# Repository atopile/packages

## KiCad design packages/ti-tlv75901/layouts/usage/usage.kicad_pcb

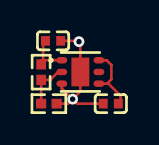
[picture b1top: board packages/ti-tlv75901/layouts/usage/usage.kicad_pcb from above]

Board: 2 copper layers, 5 parts (0 on the bottom side), 5 nets.

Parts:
C1, C2: 1µF ±10%; C0402
R1: 9.09kΩ ±1%; R0402
R2: 1.82kΩ ±1%; R0402
U1: WSON-6_L2.0-W2.0-P0.65-TL-EP

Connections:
hv: C1.1, U1.4, U1.6
lv: C1.2, U1.3
power-hv: C2.1, R1.1, U1.1
power-lv: C2.2, R2.2, U1.7
ref_out-hv: R1.2, R2.1, U1.2

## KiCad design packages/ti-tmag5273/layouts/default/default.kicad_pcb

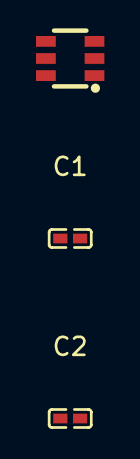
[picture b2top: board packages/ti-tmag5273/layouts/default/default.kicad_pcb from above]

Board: 2 copper layers, 3 parts (0 on the bottom side), 2 nets, no tracks yet.

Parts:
C1: 10nF ±10% 6.3V X7R; C0402
C2: 100nF ±10% 6.3V X7R; C0402
U1: SOT-23-6_L2.9-W1.6-P0.95-LS2.8-BR

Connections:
VCC: C1.1, C2.1, U1.4
gnd: C1.2, C2.2, U1.2

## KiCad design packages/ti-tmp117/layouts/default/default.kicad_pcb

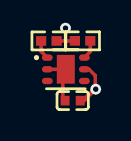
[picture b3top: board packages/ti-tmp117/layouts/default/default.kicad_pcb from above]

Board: 2 copper layers, 4 parts (0 on the bottom side), 4 nets.

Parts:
C1: 100nF; C0402
R1, R2: 10kΩ; R0402
U1: WSON-6_L2.0-W2.0-P0.65-TL-EP

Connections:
SCL: R1.1, U1.1
SDA: R2.1, U1.6
hv: C1.1, R1.2, R2.2, U1.5
lv: C1.2, U1.2, U1.4, U1.7

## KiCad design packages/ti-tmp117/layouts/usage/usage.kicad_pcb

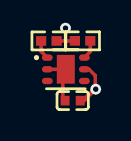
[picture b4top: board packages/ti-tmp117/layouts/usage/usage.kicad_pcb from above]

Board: 2 copper layers, 4 parts (0 on the bottom side), 4 nets.

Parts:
C1: 100nF; C0402
R3, R4: 10kΩ; R0402
U1: WSON-6_L2.0-W2.0-P0.65-TL-EP

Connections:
SCL: R3.1, U1.1
SDA: R4.1, U1.6
hv: C1.1, R3.2, R4.2, U1.5
lv: C1.2, U1.2, U1.4, U1.7

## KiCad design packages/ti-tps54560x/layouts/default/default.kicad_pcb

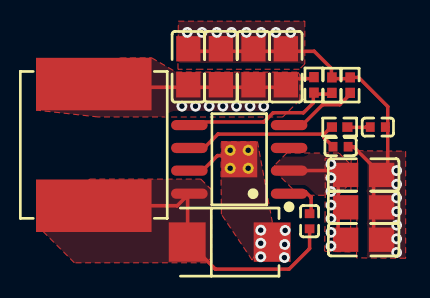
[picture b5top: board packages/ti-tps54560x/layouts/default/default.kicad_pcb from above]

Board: 2 copper layers, 17 parts (0 on the bottom side), 9 nets.

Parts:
C1: 100nF ±10%; C0402
C2: 4.7nF ±5%; C0402
C3: 10pF ±5%; C0402
C4, C5, C6: 10µF ±10%; C0805
C7, C8, C9, C10: 22µF ±20%; C0805
D1: SMB_L4.6-W3.6-LS5.3-RD
L1: IND-SMD_L8.0-W8.0_SWPA8040S
R1: 30.1kΩ ±1%; R0402
R2: 30.9kΩ ±1%; R0402
R3: 23.7kΩ ±1%; R0402
R4: 162kΩ ±1%; R0402
U1: SOIC-8_L5.0-W4.0-P1.27-LS6.0-BL-EP2.0

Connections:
RT_CLK: R4.1, U1.4
compensation_capacitors[0]-power-hv: C2.1, R3.2
compensation_capacitors[1]-power-hv: C3.1, R3.1, U1.6
hv: C1.1, U1.1
input_caps[2]-power-hv: C4.1, C5.1, C6.1, U1.2
lv: C1.2, D1.1, L1.1, U1.8
output_caps[3]-power-hv: C7.1, C8.1, C9.1, C10.1, L1.2, R1.1
output_caps[3]-power-lv: C2.2, C3.2, C4.2, C5.2, C6.2, C7.2, C8.2, C9.2, C10.2, D1.2, R2.2, R4.2, U1.7, U1.9
ref_out-hv: R1.2, R2.1, U1.5
